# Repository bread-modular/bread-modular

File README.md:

# Bread Modular

An open-source hardware modular synthesizer format designed to be minimalistic
and cost-effective: USB-powered, breadboard-friendly, with analog/digital
modules and MIDI alongside CV & Gate.

## Find your starting point

- **Build or explore:** [modules](modules/),
  [specification](https://github.com/bread-modular/bread-modular/wiki/Specification),
  [common parts](https://github.com/bread-modular/bread-modular/wiki/Common-Parts).
- **Set up KiCad libraries:** [workspace/library setup](opt/README.md). Projects
  use the shared `opt/fp-lib-table`; initialization copies local submodules
  rather than cloning them.
- **Check/export/source parts:** [KiCad toolkit](opt/kicad-tools/README.md).
  Canonical tools, JLCPCB utilities and skills live under `opt/kicad-tools/`.

## KiCad quick start

```sh
python3 -B opt/kicad-tools/kicad_tools.py --help
python3 -B opt/kicad-tools/kicad_tools.py doctor
python3 -B opt/kicad-tools/kicad_tools.py export --help
```

Python + installed KiCad CLI; no extra packages for core tools. Private checks,
Gerber/BOM/CPL export, native netlist helpers and read-only sourcing have
[distinct requirements and safety boundaries](opt/kicad-tools/README.md).
Exports are not electrical/release/order approval; keep frozen module scripts
and production designs untouched. Historical `opt/kicad-jlcpcb` and
`.agents/skills/{kicad-workflow,jlcpcb-assembly}` resolve through
[relative compatibility symlinks](opt/kicad-tools/BUNDLING.md#canonical-layout).

Agents: start with the [KiCad workflow skill](opt/kicad-tools/skills/kicad-workflow/SKILL.md)
or [assembly skill](opt/kicad-tools/skills/jlcpcb-assembly/SKILL.md), then actual CLI help.

## Project references

[Module catalog](https://github.com/bread-modular/bread-modular/wiki/Modules) ·
[Modular MIDI](https://github.com/bread-modular/bread-modular/wiki/Modular-MIDI) ·
[PCB assembly](https://github.com/bread-modular/bread-modular/wiki/PCB-Assembly)

- [Standalone exporter / native part-number setup](opt/kicad-tools/jlcpcb/README.md)
- [Sourcing, audits and passive planning](opt/kicad-tools/jlcpcb/ASSEMBLY.md)
- [32bit-5v sourcing / release HOLD](modules/32bit-5v/verification/basic-economy/README.md)
- [16bit-5v sourcing HOLD evidence](modules/16bit-5v/verification/basic-economy/README.md)

<details>
<summary>Project image and full feature overview</summary>

- **Modular design:** Just like Eurorack.
- **USB-powered:** It can be portable.
- **Minimal design:** Cost-effective.
- **Modular MIDI support:** Communicate between modules; CV & Gate still supported.
- **Analog and digital signal paths:** It’s your choice.
- **Diverse built-in modules:** A wide range of pre-designed modules.
- **Configurable digital modules:** Voice and CV using AtTiny 1616 or ESP32.
- **Fully open source:** Schematics, PCB designs and code.
- **Ease of customization:** Create modules tailored to your needs.
- **No case required:** Use directly on a breadboard or a simple base module.

</details>

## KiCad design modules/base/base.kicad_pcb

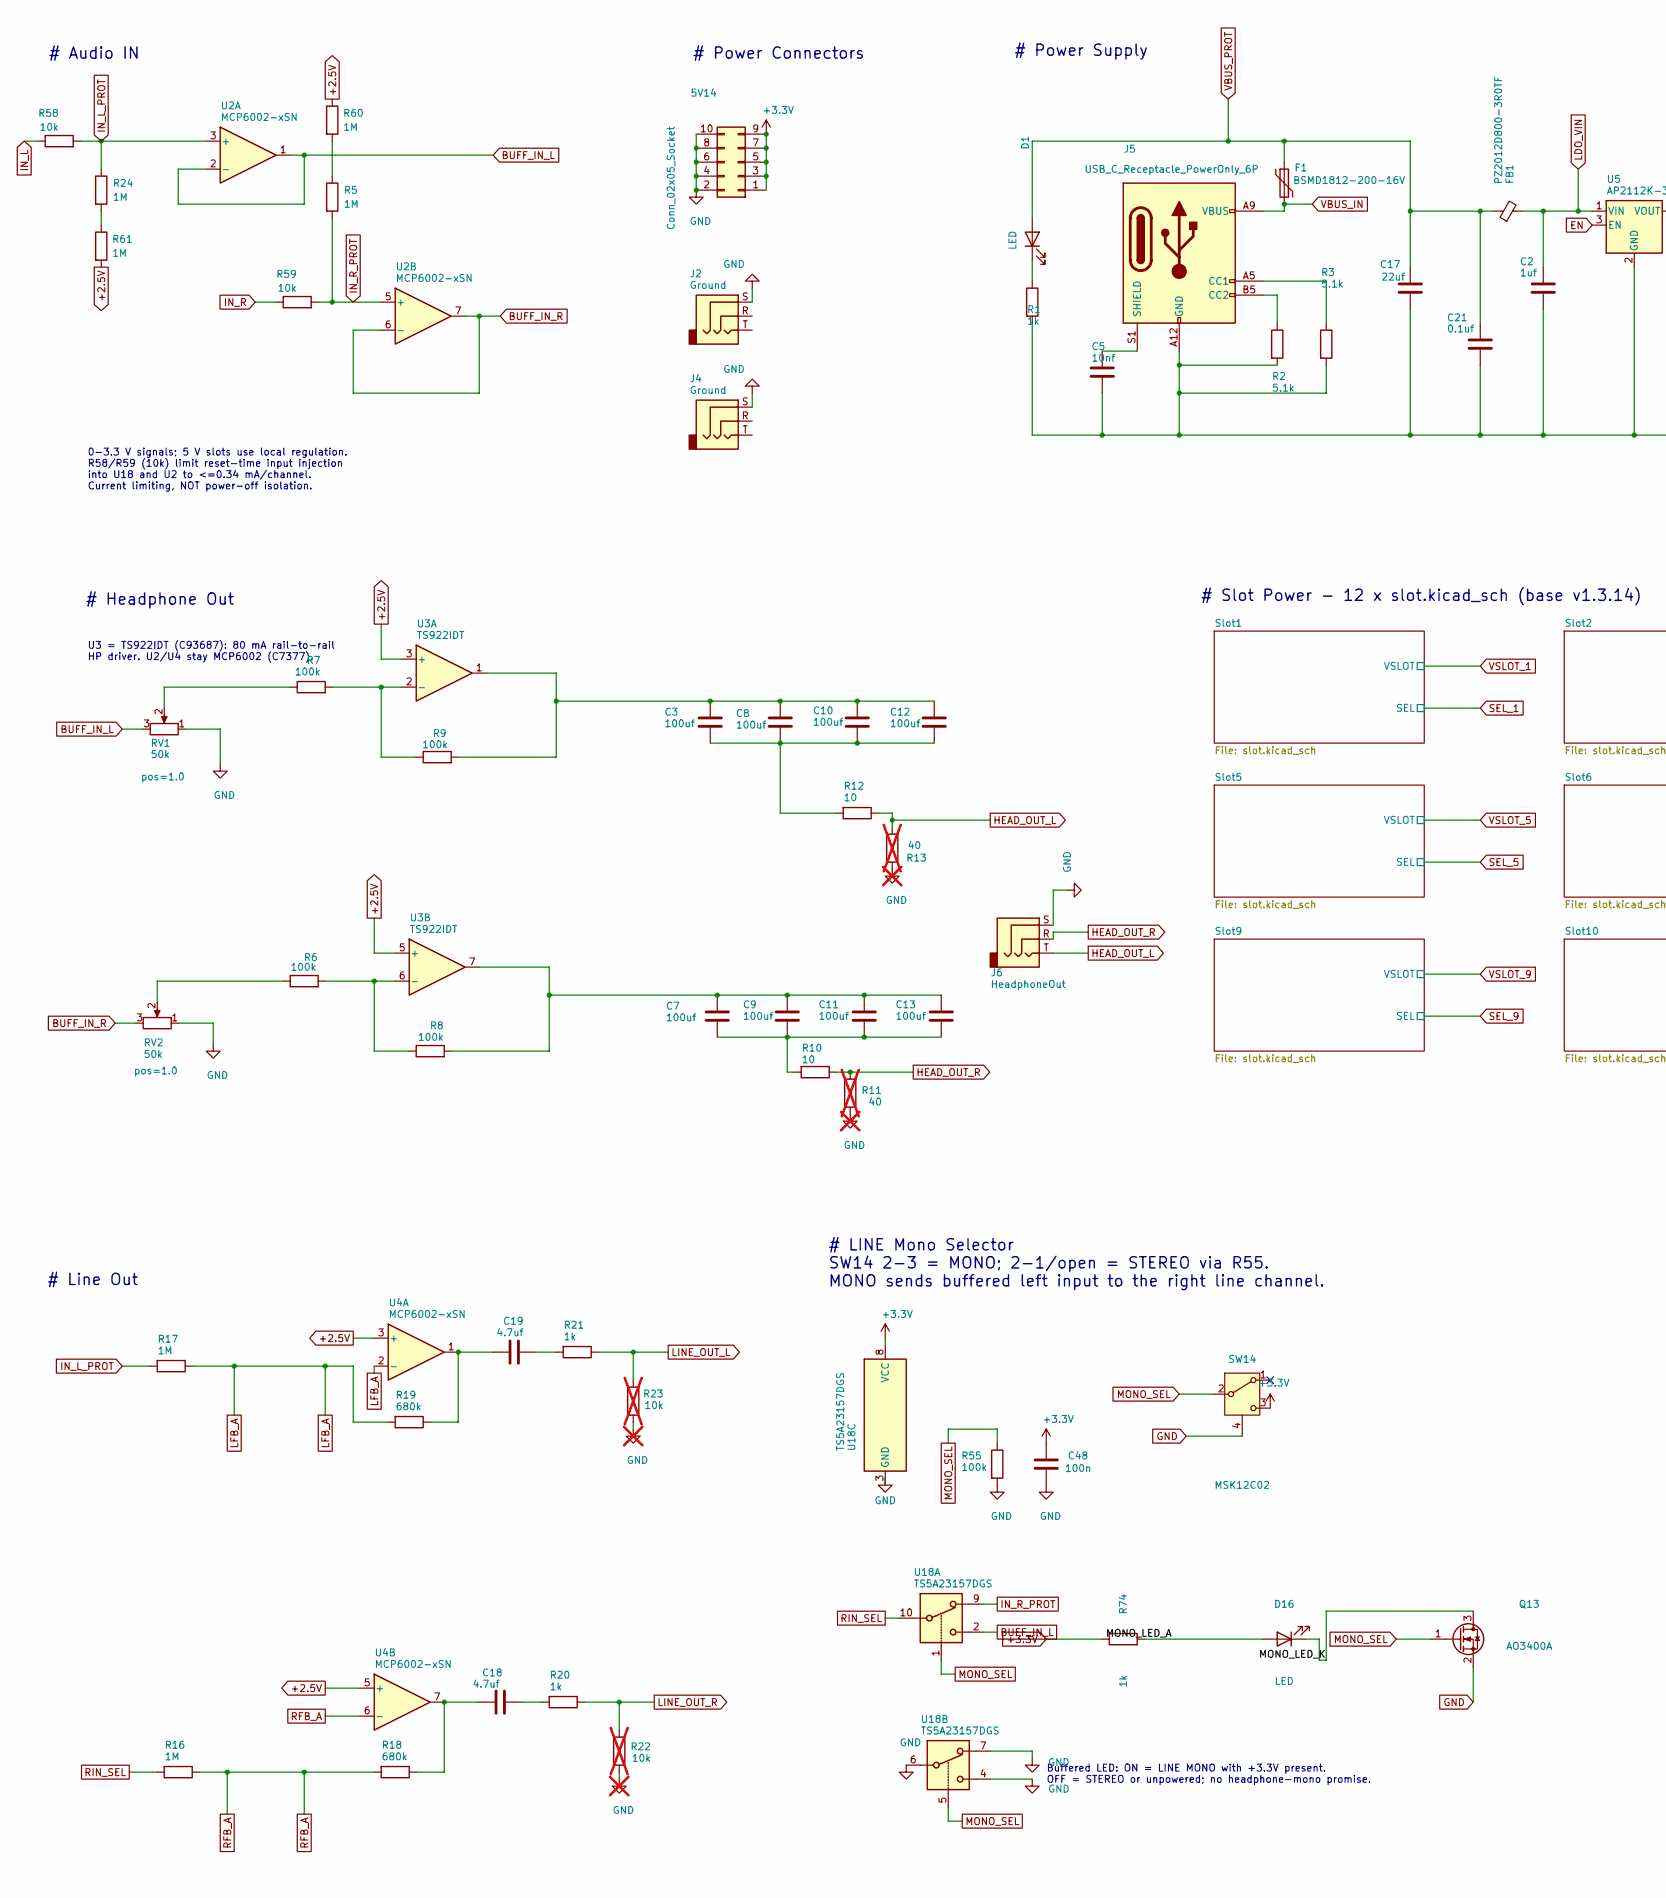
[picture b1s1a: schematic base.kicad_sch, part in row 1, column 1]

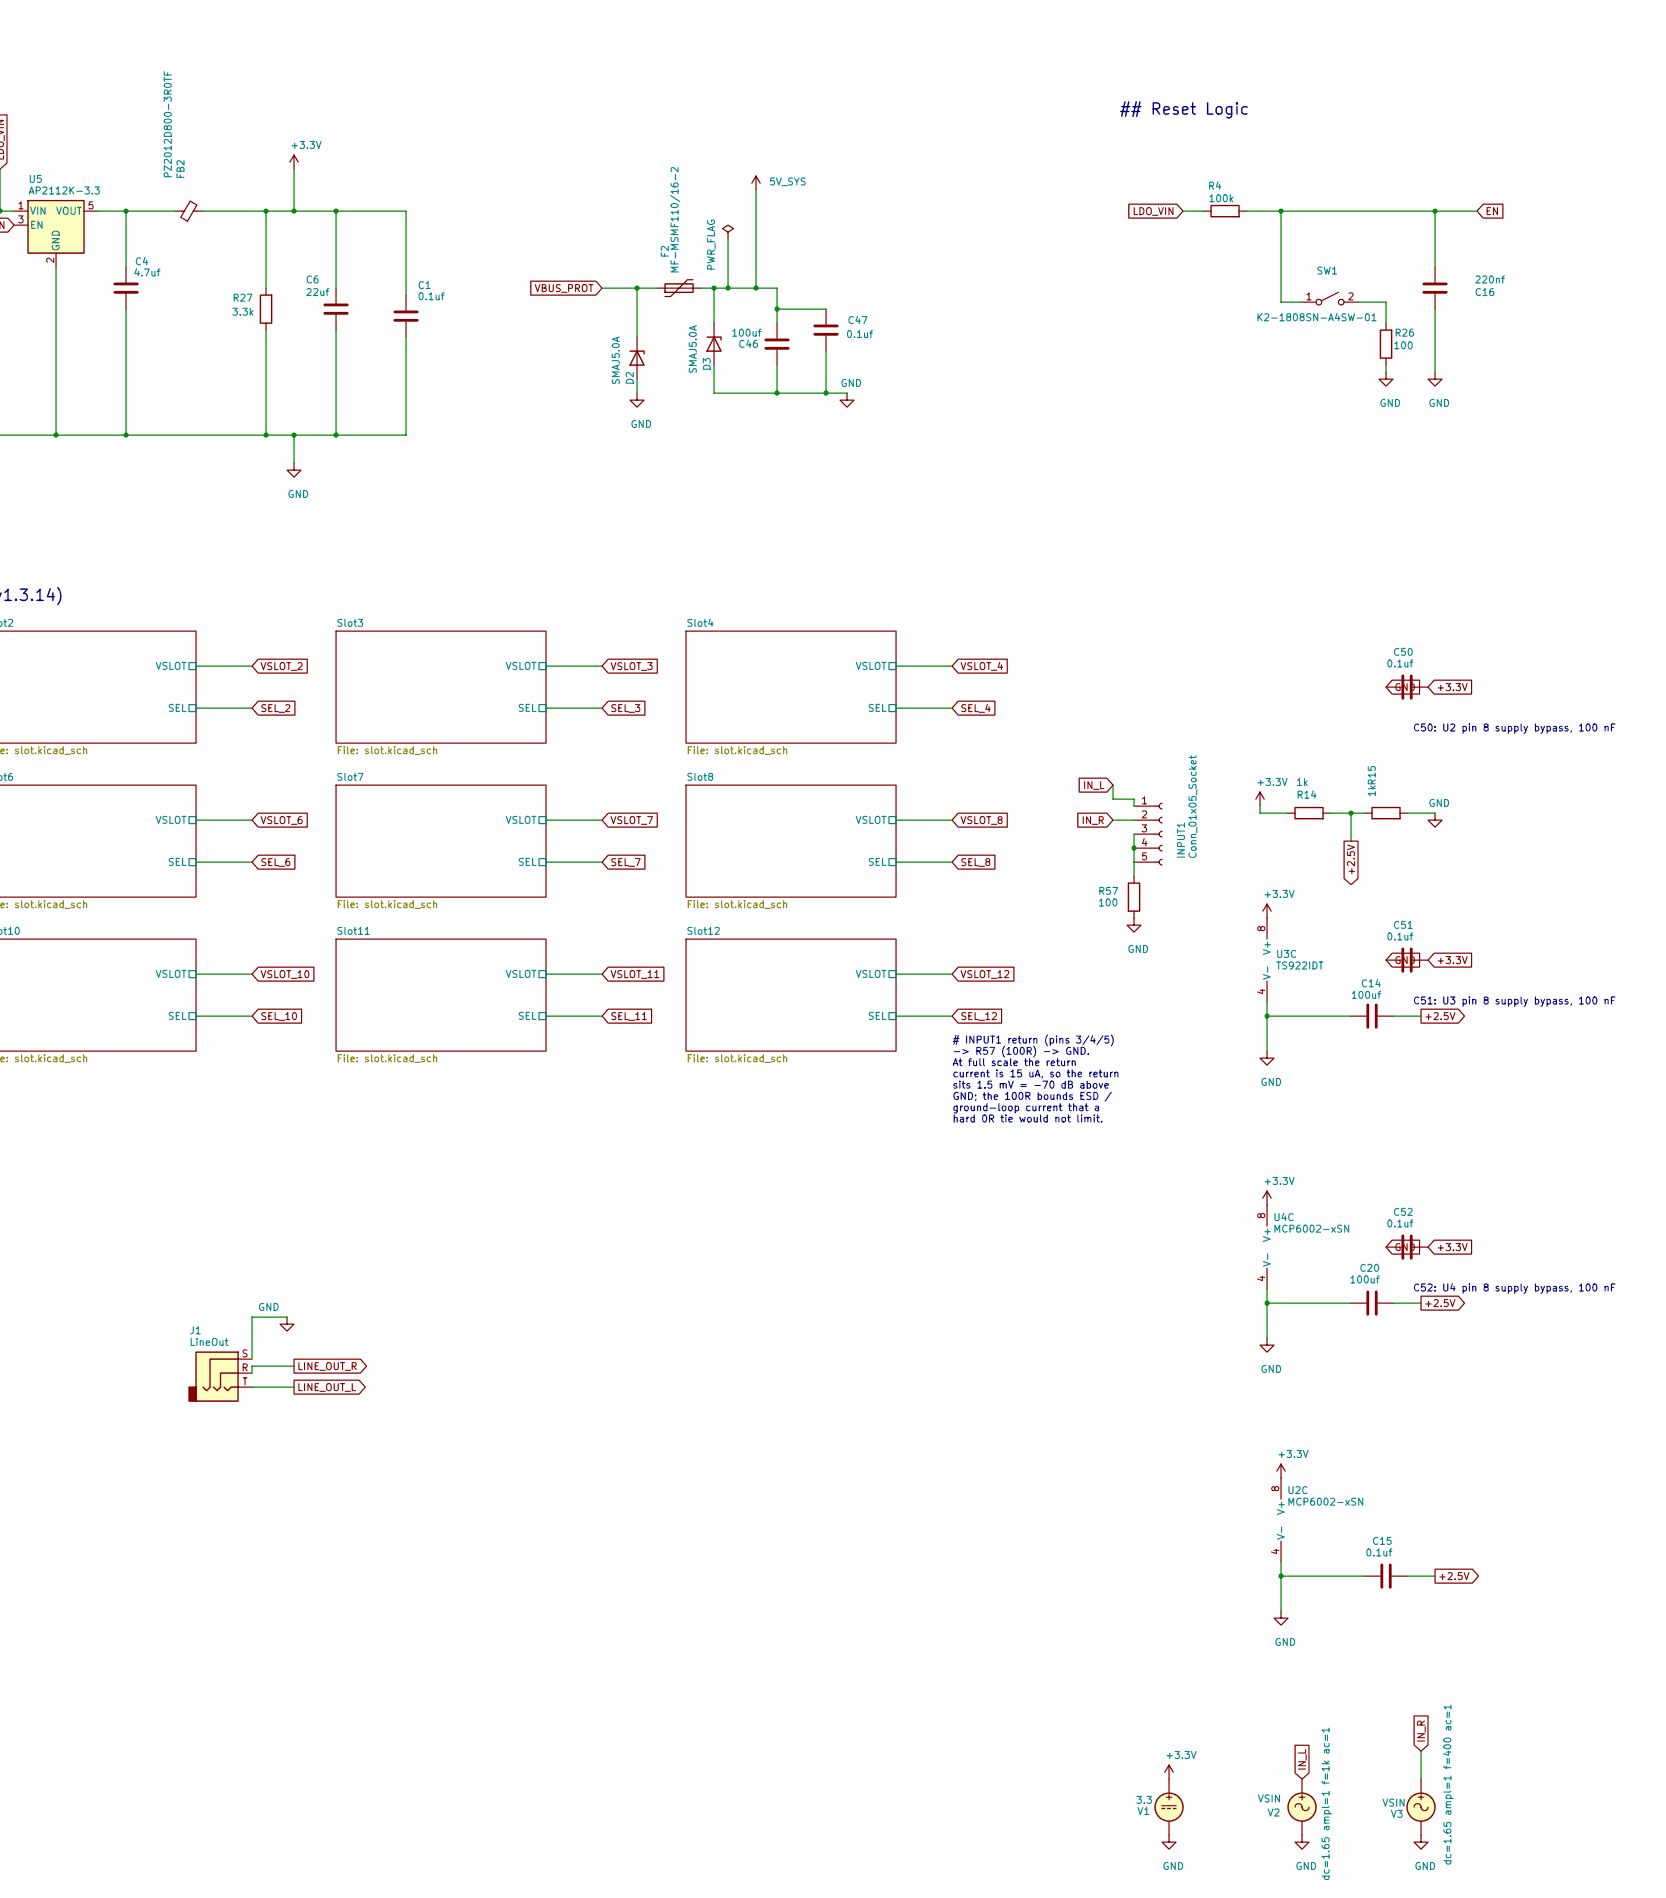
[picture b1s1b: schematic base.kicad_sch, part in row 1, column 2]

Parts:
5V14: Conn_02x05_Socket; PinSocket_2x05_P2.54mm_Vertical; MPN PZ254-2-05-Z-8.5; LCSC C2894966
C1, C15, C21, C47, C50, C51, C52: 0.1uf; C_0402_1005Metric; MPN CL05B104KO5NNNC; LCSC C1525
C2: 1uf; C_0805_2012Metric; MPN CL21B105KBFNNNE; LCSC C28323
C3, C7, C8, C9, C10, C11, C12, C13, C14, C20, C46: 100uf; C_1206_3216Metric; MPN CL31A107MQHNNNE; LCSC C15008
C4: 4.7uf; C_0805_2012Metric; MPN CL21A475KAQNNNE; LCSC C1779
C5: 10nf; C_0805_2012Metric; MPN CL21B103KBANNNC; LCSC C1710
C6, C17: 22uf; C_1206_3216Metric; MPN CL31A226KAHNNNE; LCSC C12891
C16: 220nf; C_0402_1005Metric; MPN CL05B224KO5NNNC; LCSC C16772
C18, C19: 4.7uf; C_0603_1608Metric; MPN CL10A475KO8NNNC; LCSC C19666
C48: 100n; C_0402_1005Metric; MPN CL05B104KO5NNNC; LCSC C1525
D1, D16: LED; LED_0603_1608Metric; MPN KT-0603R; LCSC C2286
D2, D3: SMAJ5.0A; D_SMA; MPN SMAJ5.0A/TR13; LCSC C78401
F1: BSMD1812-200-16V; Fuse_1812_4532Metric; MPN BSMD1812-200-16V; LCSC C883156
F2: MF-MSMF110/16-2; Fuse_1812_4532Metric; MPN MF-MSMF110/16-2; LCSC C210834
FB1, FB2: PZ2012D800-3R0TF; C_0805_2012Metric; MPN PZ2012D800-3R0TF; LCSC C12389
INPUT1: Conn_01x05_Socket; PinSocket_1x05_P2.54mm_Vertical; MPN PZ254-1-05-Z-8.5; LCSC C2894928
J1: LineOut; Jack_3.5mm_QingPu_WQP-PJ366ST_Vertical; MPN WQP-PJ366ST; LCSC NOT-JLC
J2, J4: Ground; Jack_3.5mm_QingPu_WQP-PJ366ST_Vertical; MPN WQP-PJ366ST; LCSC NOT-JLC
J5: USB_C_Receptacle_PowerOnly_6P; HRO-TYPE-C-31-M-12; MPN TYPE-C-31-M-12; LCSC C165948
J6: HeadphoneOut; Jack_3.5mm_QingPu_WQP-PJ366ST_Vertical; MPN WQP-PJ366ST; LCSC NOT-JLC
Q13: AO3400A; SOT-23; MPN AO3400A; LCSC C20917
R1, R14, R15, R20, R21, R74: 1k; R_0402_1005Metric; MPN 0402WGF1001TCE; LCSC C11702
R2, R3: 5.1k; R_0603_1608Metric; MPN 0603WAF5101T5E; LCSC C23186
R4, R6, R7, R8, R9, R55: 100k; R_0402_1005Metric; MPN 0402WGF1003TCE; LCSC C25741
R5, R16, R17, R24, R60, R61: 1M; R_0402_1005Metric; MPN 0402WGF1004TCE; LCSC C26083
R10, R12: 10; R_1206_3216Metric; MPN 1206W4F100JT5E; LCSC C17903
R11: 40; MPN N/A-SIM; LCSC N/A-SIM; not fitted
R13: 40; R_0402_1005Metric; MPN N/A-SIM; LCSC N/A-SIM; not fitted
R18, R19: 680k; R_0603_1608Metric; MPN 0603WAF6803T5E; LCSC C25822
R22, R23: 10k; MPN N/A-SIM; LCSC N/A-SIM; not fitted
R26, R57: 100; R_0402_1005Metric; MPN 0402WGF1000TCE; LCSC C25076
R27: 3.3k; R_0402_1005Metric; MPN 0402WGF3301TCE; LCSC C25890
R58, R59: 10k; R_0402_1005Metric; MPN 0402WGF1002TCE; LCSC C25744
RV1, RV2: 50k; Potentiometer_RV09; MPN RV09-50K; LCSC NOT-JLC
SW1: K2-1808SN-A4SW-01; MPN K2-1808SN-A4SW-01; LCSC C92589
SW14: MSK12C02; SW_SPDT_Shouhan_MSK12C02_C431540; MPN MSK12C02; LCSC C431540
U2, U4: MCP6002-xSN; SOIC-8_3.9x4.9mm_P1.27mm; MPN MCP6002T-I/SN; LCSC C7377
U3: TS922IDT; SOIC-8_3.9x4.9mm_P1.27mm; MPN TS922IDT; LCSC C93687
U5: AP2112K-3.3; SOT-23-5; MPN AP2112K-3.3TRG1; LCSC C51118
U18: TS5A23157DGS; TSSOP-10_3x3mm_P0.5mm; MPN TS5A23157DGSR; LCSC C11133
V1: 3.3; MPN N/A-SIM; LCSC N/A-SIM
V2, V3: VSIN; MPN N/A-SIM; LCSC N/A-SIM

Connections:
5V_SYS: C46.1, C47.1, D3.1 (K), F2.2; also elsewhere on the board
+2.5V: C14.2, C15.2, C20.2, R14.2, R15.1, R60.1, R61.2, U3.3 (+), U3.5 (+), U4.3 (+), U4.5 (+)
+3.3V: 5V14.1, 5V14.3, 5V14.5, 5V14.7, 5V14.9, C1.1, C6.1, C48.1, C50.2, C51.2, C52.2, FB2.2, R14.1, R27.2, R74.1, SW14.3 (C), U2.8 (V+), U3.8 (V+), U4.8 (V+), U18.8 (VCC), V1.1; also elsewhere on the board
/MONO_LED_A: D16.2 (A), R74.2
/MONO_LED_K: D16.1 (K), Q13.3 (D)
BUFF_IN_L: RV1.3, U2.1, U2.2 (-), U18.2
BUFF_IN_R: RV2.3, U2.6 (-), U2.7
EN: C16.1, R4.2, SW1.1 (A), U5.3 (EN)
GND: 5V14.2, 5V14.4, 5V14.6, 5V14.8, 5V14.10, C1.2, C2.2, C4.2, C5.2, C6.2, C14.1, C15.1, C16.2, C17.2, C20.1, C21.2, C46.2, C47.2, C48.2, C50.1, C51.1, C52.1, D2.2 (A), D3.2 (A), J1.S, J2.S, J4.S, J5.A12 (GND), J5.B12 (GND), J6.S, Q13.2 (S), R1.2, R2.2, R3.2, R11.1, R13.1, R15.2, R22.1, R23.1, R26.1, R27.1, R55.2, R57.2, RV1.1, RV2.1, SW14.4 (SHIELD), U2.4 (V-), U3.4 (V-), U4.4 (V-), U5.2 (GND), U18.3 (GND), U18.4, U18.6, U18.7, V1.2, V2.2, V3.2; also elsewhere on the board
HEAD_OUT_L: J6.T, R12.1, R13.2
HEAD_OUT_R: J6.R, R10.1, R11.2
IN_L: INPUT1.1, R58.1, V2.1
IN_L_PROT: R17.2, R24.1, R58.2, U2.3 (+)
IN_R: INPUT1.2, R59.1, V3.1
IN_R_PROT: R5.2, R59.2, U2.5 (+), U18.9
LDO_VIN: C2.1, FB1.2, R4.1, U5.1 (VIN)
LFB_A: R17.1, R19.2, U4.2 (-)
LINE_OUT_L: J1.T, R21.1, R23.2
LINE_OUT_R: J1.R, R20.1, R22.2
MONO_SEL: Q13.1 (G), R55.1, SW14.2 (B), U18.1, U18.5
unnamed: C3.1, C8.1, C10.1, C12.1, R9.2, U3.1
unnamed: C3.2, C8.2, C10.2, C12.2, R12.2
unnamed: C7.1, C9.1, C11.1, C13.1, R8.2, U3.7
unnamed: C7.2, C9.2, C11.2, C13.2, R10.2
unnamed: C18.1, R18.1, U4.7
unnamed: C18.2, R20.2
unnamed: C19.1, R19.1, U4.1
unnamed: C19.2, R21.2
unnamed: D1.1 (K), R1.1
unnamed: INPUT1.3, INPUT1.4, INPUT1.5, R57.1
unnamed: J5.A5 (CC1), R3.1
unnamed: J5.B5 (CC2), R2.1
unnamed: C5.1, J5.S1 (SHIELD)
unnamed: R5.1, R60.2
unnamed: R6.1, RV2.2
unnamed: R7.1, RV1.2
unnamed: R24.2, R61.1
unnamed: R26.2, SW1.2 (B)
unnamed: R7.2, R9.1, U3.2 (-)
unnamed: R6.2, R8.1, U3.6 (-)
unnamed: C4.1, FB2.1, U5.5 (VOUT)
RFB_A: R16.1, R18.2, U4.6 (-)
RIN_SEL: R16.2, U18.10
VBUS_IN: F1.2, J5.A9 (VBUS), J5.B9 (VBUS)
VBUS_PROT: C17.1, C21.1, D1.2 (A), D2.1 (K), F1.1, F2.1, FB1.1; also elsewhere on the board

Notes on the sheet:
Buffered LED: ON = LINE MONO with +3.3V present. OFF = STEREO or unpowered; no headphone-mono promise.
## Reset Logic
# Slot Power - 12 x slot.kicad_sch (base v1.3.14)
# INPUT1 return (pins 3/4/5) -> R57 (100R) -> GND. At full scale the return current is 15 uA, so the return sits 1.5 mV = -70 dB above GND; the 100R bounds ESD / ground-loop current that a hard 0R tie would not limit.
# Power Supply
# Audio IN
C51: U3 pin 8 supply bypass, 100 nF
0-3.3 V signals; 5 V slots use local regulation. R58/R59 (10k) limit reset-time input injection into U18 and U2 to <=0.34 mA/channel. Current limiting, NOT power-off isolation.
U3 = TS922IDT (C93687): 80 mA rail-to-rail HP driver. U2/U4 stay MCP6002 (C7377).
C50: U2 pin 8 supply bypass, 100 nF
# LINE Mono Selector SW14 2-3 = MONO; 2-1/open = STEREO via R55. MONO sends buffered left input to the right line channel.
# Headphone Out
# Power Connectors
# Line Out
C52: U4 pin 8 supply bypass, 100 nF

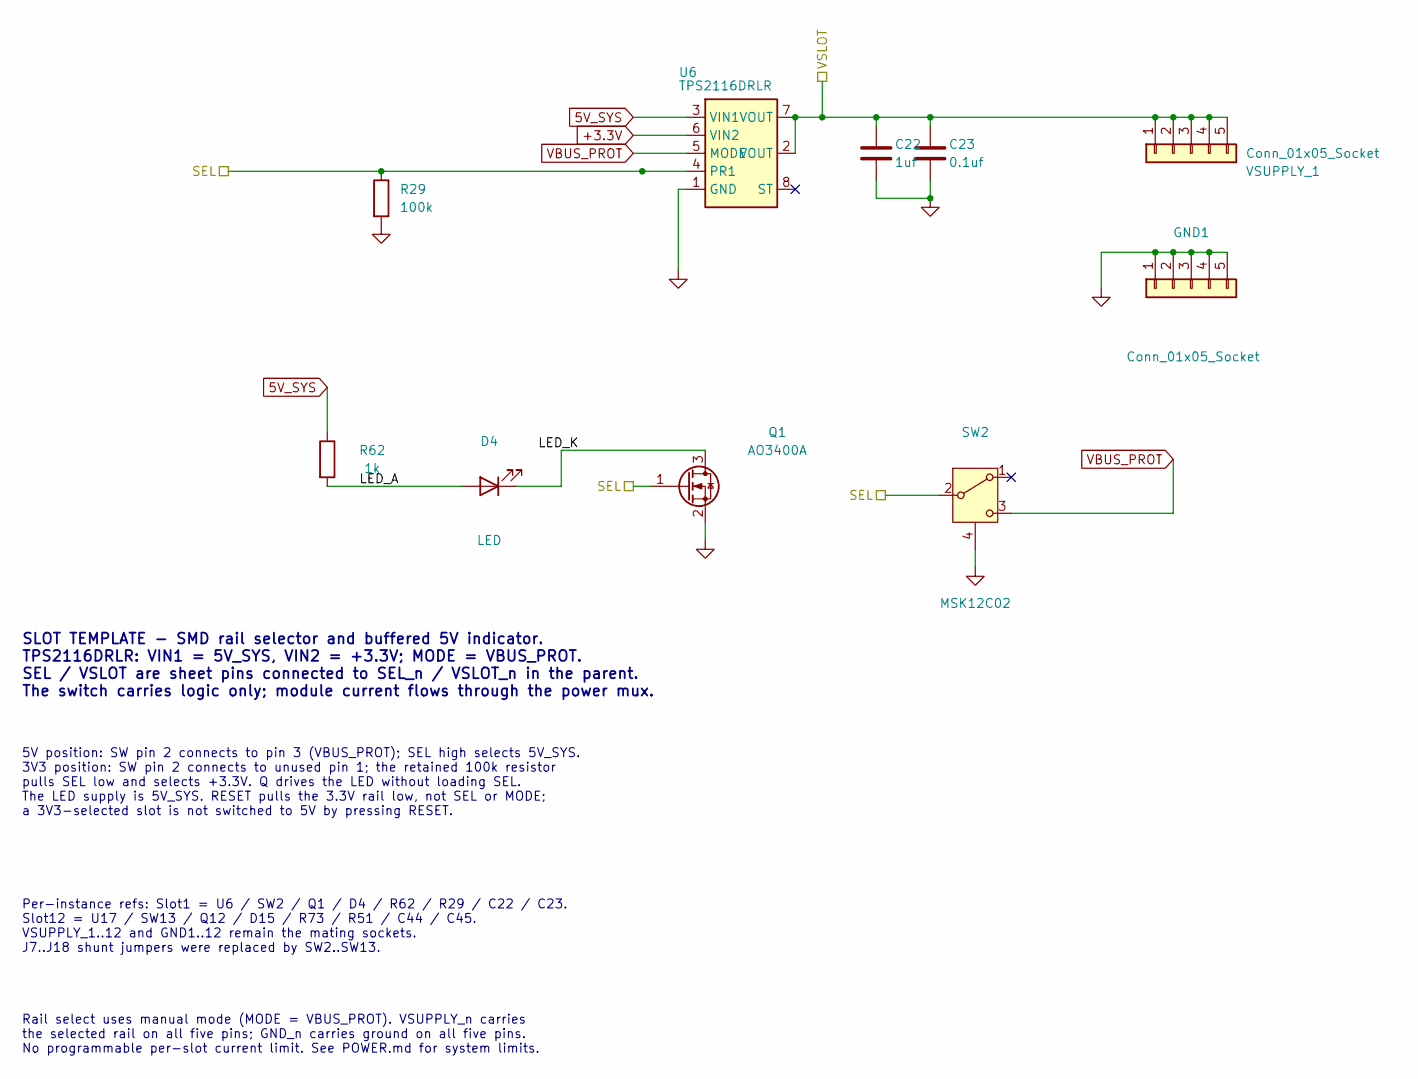
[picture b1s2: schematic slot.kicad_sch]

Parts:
C22: 1uf; C_0402_1005Metric; MPN CL05A105KA5NQNC; LCSC C52923
C23: 0.1uf; C_0402_1005Metric; MPN CL05B104KO5NNNC; LCSC C1525
D4: LED; LED_0603_1608Metric; MPN KT-0603R; LCSC C2286
GND1: Conn_01x05_Socket; Power_Connector; MPN PZ254-1-05-Z-8.5; LCSC C2894928
Q1: AO3400A; SOT-23; MPN AO3400A; LCSC C20917
R29: 100k; R_0402_1005Metric; MPN 0402WGF1003TCE; LCSC C25741
R62: 1k; R_0402_1005Metric; MPN 0402WGF1001TCE; LCSC C11702
SW2: MSK12C02; SW_SPDT_Shouhan_MSK12C02_C431540; MPN MSK12C02; LCSC C431540
U6: TPS2116DRLR; SOT-583-8; MPN TPS2116DRLR; LCSC C3235557
VSUPPLY_1: Conn_01x05_Socket; Power_Connector; MPN PZ254-1-05-Z-8.5; LCSC C2894928

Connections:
5V_SYS: R62.1, U6.3 (VIN1); also elsewhere on the board
+3.3V: U6.6 (VIN2); also elsewhere on the board
/Slot1/LED_A: D4.2 (A), R62.2
/Slot1/LED_K: D4.1 (K), Q1.3 (D)
GND: C22.2, C23.2, GND1.1, GND1.2, GND1.3, GND1.4, GND1.5, Q1.2 (S), R29.2, SW2.4 (SHIELD), U6.1 (GND); also elsewhere on the board
SEL_1: Q1.1 (G), R29.1, SW2.2 (B), U6.4 (PR1)
VBUS_PROT: SW2.3 (C), U6.5 (MODE); also elsewhere on the board
VSLOT_1: C22.1, C23.1, U6.2 (VOUT), U6.7 (VOUT), VSUPPLY_1.1, VSUPPLY_1.2, VSUPPLY_1.3, VSUPPLY_1.4, VSUPPLY_1.5

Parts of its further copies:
C24, C26, C28, C30, C32, C34, C36, C38, C40, C42, C44: 1uf; C_0402_1005Metric; MPN CL05A105KA5NQNC; LCSC C52923
C25, C27, C29, C31, C33, C35, C37, C39, C41, C43, C45: 0.1uf; C_0402_1005Metric; MPN CL05B104KO5NNNC; LCSC C1525
D5, D6, D7, D8, D9, D10, D11, D12, D13, D14, D15: LED; LED_0603_1608Metric; MPN KT-0603R; LCSC C2286
GND2, GND3, GND4, GND5, GND6, GND7, GND8, GND9, GND10, GND11, GND12: Conn_01x05_Socket; Power_Connector; MPN PZ254-1-05-Z-8.5; LCSC C2894928
Q2, Q3, Q4, Q5, Q6, Q7, Q8, Q9, Q10, Q11, Q12: AO3400A; SOT-23; MPN AO3400A; LCSC C20917
R31, R33, R35, R37, R39, R41, R43, R45, R47, R49, R51: 100k; R_0402_1005Metric; MPN 0402WGF1003TCE; LCSC C25741
R63, R64, R65, R66, R67, R68, R69, R70, R71, R72, R73: 1k; R_0402_1005Metric; MPN 0402WGF1001TCE; LCSC C11702
SW3, SW4, SW5, SW6, SW7, SW8, SW9, SW10, SW11, SW12, SW13: MSK12C02; SW_SPDT_Shouhan_MSK12C02_C431540; MPN MSK12C02; LCSC C431540
U7, U8, U9, U10, U11, U12, U13, U14, U15, U16, U17: TPS2116DRLR; SOT-583-8; MPN TPS2116DRLR; LCSC C3235557
VSUPPLY_2, VSUPPLY_3, VSUPPLY_4, VSUPPLY_5, VSUPPLY_6, VSUPPLY_7, VSUPPLY_8, VSUPPLY_9, VSUPPLY_10, VSUPPLY_11, VSUPPLY_12: Conn_01x05_Socket; Power_Connector; MPN PZ254-1-05-Z-8.5; LCSC C2894928

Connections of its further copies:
5V_SYS: R63.1, R64.1, R65.1, R66.1, R67.1, R68.1, R69.1, R70.1, R71.1, R72.1, R73.1, U7.3 (VIN1), U8.3 (VIN1), U9.3 (VIN1), U10.3 (VIN1), U11.3 (VIN1), U12.3 (VIN1), U13.3 (VIN1), U14.3 (VIN1), U15.3 (VIN1), U16.3 (VIN1), U17.3 (VIN1); also elsewhere on the board
+3.3V: U7.6 (VIN2), U8.6 (VIN2), U9.6 (VIN2), U10.6 (VIN2), U11.6 (VIN2), U12.6 (VIN2), U13.6 (VIN2), U14.6 (VIN2), U15.6 (VIN2), U16.6 (VIN2), U17.6 (VIN2); also elsewhere on the board
/Slot2/LED_A: D5.2 (A), R63.2
/Slot2/LED_K: D5.1 (K), Q2.3 (D)
/Slot3/LED_A: D6.2 (A), R64.2
/Slot3/LED_K: D6.1 (K), Q3.3 (D)
/Slot4/LED_A: D7.2 (A), R65.2
/Slot4/LED_K: D7.1 (K), Q4.3 (D)
/Slot5/LED_A: D8.2 (A), R66.2
/Slot5/LED_K: D8.1 (K), Q5.3 (D)
/Slot6/LED_A: D9.2 (A), R67.2
/Slot6/LED_K: D9.1 (K), Q6.3 (D)
/Slot7/LED_A: D10.2 (A), R68.2
/Slot7/LED_K: D10.1 (K), Q7.3 (D)
/Slot8/LED_A: D11.2 (A), R69.2
/Slot8/LED_K: D11.1 (K), Q8.3 (D)
/Slot9/LED_A: D12.2 (A), R70.2
/Slot9/LED_K: D12.1 (K), Q9.3 (D)
/Slot10/LED_A: D13.2 (A), R71.2
/Slot10/LED_K: D13.1 (K), Q10.3 (D)
/Slot11/LED_A: D14.2 (A), R72.2
/Slot11/LED_K: D14.1 (K), Q11.3 (D)
/Slot12/LED_A: D15.2 (A), R73.2
/Slot12/LED_K: D15.1 (K), Q12.3 (D)
GND: C24.2, C25.2, C26.2, C27.2, C28.2, C29.2, C30.2, C31.2, C32.2, C33.2, C34.2, C35.2, C36.2, C37.2, C38.2, C39.2, C40.2, C41.2, C42.2, C43.2, C44.2, C45.2, GND2.1, GND2.2, GND2.3, GND2.4, GND2.5, GND3.1, GND3.2, GND3.3, GND3.4, GND3.5, GND4.1, GND4.2, GND4.3, GND4.4, GND4.5, GND5.1, GND5.2, GND5.3, GND5.4, GND5.5, GND6.1, GND6.2, GND6.3, GND6.4, GND6.5, GND7.1, GND7.2, GND7.3, GND7.4, GND7.5, GND8.1, GND8.2, GND8.3, GND8.4, GND8.5, GND9.1, GND9.2, GND9.3, GND9.4, GND9.5, GND10.1, GND10.2, GND10.3, GND10.4, GND10.5, GND11.1, GND11.2, GND11.3, GND11.4, GND11.5, GND12.1, GND12.2, GND12.3, GND12.4, GND12.5, Q2.2 (S), Q3.2 (S), Q4.2 (S), Q5.2 (S), Q6.2 (S), Q7.2 (S), Q8.2 (S), Q9.2 (S), Q10.2 (S), Q11.2 (S), Q12.2 (S), R31.2, R33.2, R35.2, R37.2, R39.2, R41.2, R43.2, R45.2, R47.2, R49.2, R51.2, SW3.4 (SHIELD), SW4.4 (SHIELD), SW5.4 (SHIELD), SW6.4 (SHIELD), SW7.4 (SHIELD), SW8.4 (SHIELD), SW9.4 (SHIELD), SW10.4 (SHIELD), SW11.4 (SHIELD), SW12.4 (SHIELD), SW13.4 (SHIELD), U7.1 (GND), U8.1 (GND), U9.1 (GND), U10.1 (GND), U11.1 (GND), U12.1 (GND), U13.1 (GND), U14.1 (GND), U15.1 (GND), U16.1 (GND), U17.1 (GND); also elsewhere on the board
SEL_2: Q2.1 (G), R31.1, SW3.2 (B), U7.4 (PR1)
SEL_3: Q3.1 (G), R33.1, SW4.2 (B), U8.4 (PR1)
SEL_4: Q4.1 (G), R35.1, SW5.2 (B), U9.4 (PR1)
SEL_5: Q5.1 (G), R37.1, SW6.2 (B), U10.4 (PR1)
SEL_6: Q6.1 (G), R39.1, SW7.2 (B), U11.4 (PR1)
SEL_7: Q7.1 (G), R41.1, SW8.2 (B), U12.4 (PR1)
SEL_8: Q8.1 (G), R43.1, SW9.2 (B), U13.4 (PR1)
SEL_9: Q9.1 (G), R45.1, SW10.2 (B), U14.4 (PR1)
SEL_10: Q10.1 (G), R47.1, SW11.2 (B), U15.4 (PR1)
SEL_11: Q11.1 (G), R49.1, SW12.2 (B), U16.4 (PR1)
SEL_12: Q12.1 (G), R51.1, SW13.2 (B), U17.4 (PR1)
VBUS_PROT: SW3.3 (C), SW4.3 (C), SW5.3 (C), SW6.3 (C), SW7.3 (C), SW8.3 (C), SW9.3 (C), SW10.3 (C), SW11.3 (C), SW12.3 (C), SW13.3 (C), U7.5 (MODE), U8.5 (MODE), U9.5 (MODE), U10.5 (MODE), U11.5 (MODE), U12.5 (MODE), U13.5 (MODE), U14.5 (MODE), U15.5 (MODE), U16.5 (MODE), U17.5 (MODE); also elsewhere on the board
VSLOT_2: C24.1, C25.1, U7.2 (VOUT), U7.7 (VOUT), VSUPPLY_2.1, VSUPPLY_2.2, VSUPPLY_2.3, VSUPPLY_2.4, VSUPPLY_2.5
VSLOT_3: C26.1, C27.1, U8.2 (VOUT), U8.7 (VOUT), VSUPPLY_3.1, VSUPPLY_3.2, VSUPPLY_3.3, VSUPPLY_3.4, VSUPPLY_3.5
VSLOT_4: C28.1, C29.1, U9.2 (VOUT), U9.7 (VOUT), VSUPPLY_4.1, VSUPPLY_4.2, VSUPPLY_4.3, VSUPPLY_4.4, VSUPPLY_4.5
VSLOT_5: C30.1, C31.1, U10.2 (VOUT), U10.7 (VOUT), VSUPPLY_5.1, VSUPPLY_5.2, VSUPPLY_5.3, VSUPPLY_5.4, VSUPPLY_5.5
VSLOT_6: C32.1, C33.1, U11.2 (VOUT), U11.7 (VOUT), VSUPPLY_6.1, VSUPPLY_6.2, VSUPPLY_6.3, VSUPPLY_6.4, VSUPPLY_6.5
VSLOT_7: C34.1, C35.1, U12.2 (VOUT), U12.7 (VOUT), VSUPPLY_7.1, VSUPPLY_7.2, VSUPPLY_7.3, VSUPPLY_7.4, VSUPPLY_7.5
VSLOT_8: C36.1, C37.1, U13.2 (VOUT), U13.7 (VOUT), VSUPPLY_8.1, VSUPPLY_8.2, VSUPPLY_8.3, VSUPPLY_8.4, VSUPPLY_8.5
VSLOT_9: C38.1, C39.1, U14.2 (VOUT), U14.7 (VOUT), VSUPPLY_9.1, VSUPPLY_9.2, VSUPPLY_9.3, VSUPPLY_9.4, VSUPPLY_9.5
VSLOT_10: C40.1, C41.1, U15.2 (VOUT), U15.7 (VOUT), VSUPPLY_10.1, VSUPPLY_10.2, VSUPPLY_10.3, VSUPPLY_10.4, VSUPPLY_10.5
VSLOT_11: C42.1, C43.1, U16.2 (VOUT), U16.7 (VOUT), VSUPPLY_11.1, VSUPPLY_11.2, VSUPPLY_11.3, VSUPPLY_11.4, VSUPPLY_11.5
VSLOT_12: C44.1, C45.1, U17.2 (VOUT), U17.7 (VOUT), VSUPPLY_12.1, VSUPPLY_12.2, VSUPPLY_12.3, VSUPPLY_12.4, VSUPPLY_12.5

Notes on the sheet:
SLOT TEMPLATE - SMD rail selector and buffered 5V indicator. TPS2116DRLR: VIN1 = 5V_SYS, VIN2 = +3.3V; MODE = VBUS_PROT. SEL / VSLOT are sheet pins connected to SEL_n / VSLOT_n in the parent. The switch carries logic only; module current flows through the power mux.
Rail select uses manual mode (MODE = VBUS_PROT). VSUPPLY_n carries the selected rail on all five pins; GND_n carries ground on all five pins. No programmable per-slot current limit. See POWER.md for system limits.
5V position: SW pin 2 connects to pin 3 (VBUS_PROT); SEL high selects 5V_SYS. 3V3 position: SW pin 2 connects to unused pin 1; the retained 100k resistor pulls SEL low and selects +3.3V. Q drives the LED without loading SEL. The LED supply is 5V_SYS. RESET pulls the 3.3V rail low, not SEL or MODE; 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
Per-instance refs: Slot1 = U6 / SW2 / Q1 / D4 / R62 / R29 / C22 / C23. Slot12 = U17 / SW13 / Q12 / D15 / R73 / R51 / C44 / C45. VSUPPLY_1..12 and GND1..12 remain the mating sockets. J7..J18 shunt jumpers were replaced by SW2..SW13.

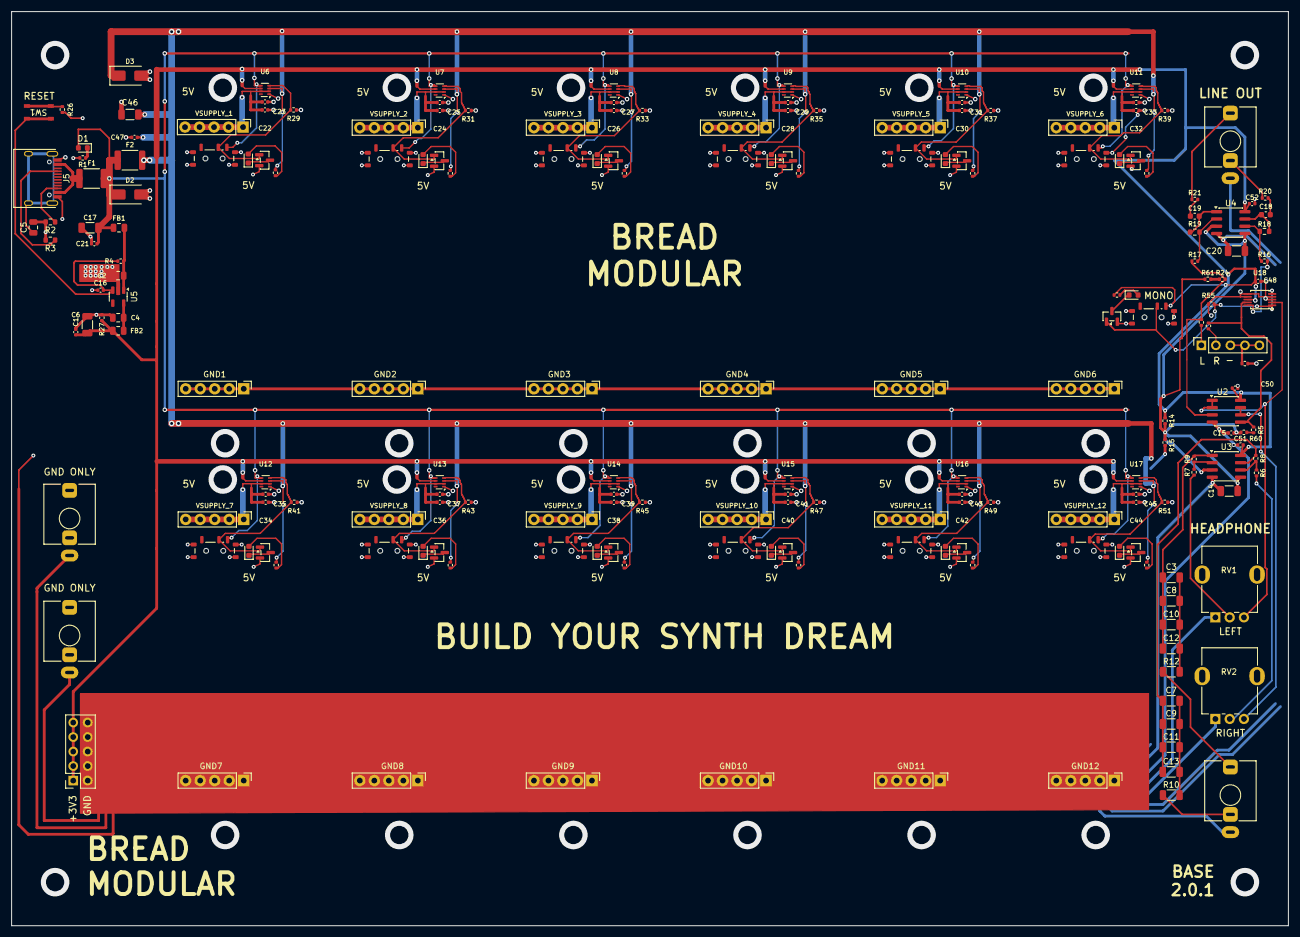
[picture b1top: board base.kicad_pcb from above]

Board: 2 copper layers, 223.5 x 160.0 mm, 201 parts (0 on the bottom side), 93 nets.

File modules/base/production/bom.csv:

Designator,Footprint,Quantity,Value,LCSC Part #,DNP
5V14,Connector_PinSocket_2.54mm:PinSocket_2x05_P2.54mm_Vertical,1,Conn_02x05_Socket,NOT-JLC,
"C1,C15,C21,C23,C25,C27,C29,C31,C33,C35,C37,C39,C41,C43,C45,C47,C50,C51,C52",Capacitor_SMD:C_0402_1005Metric,19,0.1uf,C1525,
C2,Capacitor_SMD:C_0805_2012Metric,1,1uf,C28323,
"C3,C7,C8,C9,C10,C11,C12,C13,C14,C20",Capacitor_SMD:C_1206_3216Metric,10,100uf,C15008,
C4,Capacitor_SMD:C_0805_2012Metric,1,4.7uf,C1779,
C5,Capacitor_SMD:C_0805_2012Metric,1,10nf,C472806,
"C6,C17",Capacitor_SMD:C_1206_3216Metric,2,22uf,C90146,
C16,Capacitor_SMD:C_0402_1005Metric,1,220nf,C16772,
"C18,C19",Capacitor_SMD:C_0603_1608Metric,2,4.7uf,C1705,
"C22,C24,C26,C28,C30,C32,C34,C36,C38,C40,C42,C44",Capacitor_SMD:C_0402_1005Metric,12,1uf,C52923,
C46,Capacitor_SMD:C_1210_3225Metric,1,100uf,C394395,
C48,Capacitor_SMD:C_0402_1005Metric,1,100n,C1525,
D1,LED_SMD:LED_0603_1608Metric,1,LED,C2286,
"D2,D3",Diode_SMD:D_SMA,2,SMAJ5.0A,C78401,
F1,Fuse:Fuse_1812_4532Metric,1,BSMD1812-200-16V,C883156,
F2,Fuse:Fuse_1812_4532Metric,1,MF-MSMF110/16-2,C210834,
"FB1,FB2",Capacitor_SMD:C_0805_2012Metric,2,PZ2012D800-3R0TF,C12389,
"GND1,GND2,GND3,GND4,GND5,GND6,GND7,GND8,GND9,GND10,GND11,GND12,VSUPPLY_1,VSUPPLY_2,VSUPPLY_3,VSUPPLY_4,VSUPPLY_5,VSUPPLY_6,VSUPPLY_7,VSUPPLY_8,VSUPPLY_9,VSUPPLY_10,VSUPPLY_11,VSUPPLY_12",BreadModular_MISC:Power_Connector,24,Conn_01x05_Socket,NOT-JLC,
INPUT1,Connector_PinSocket_2.54mm:PinSocket_1x05_P2.54mm_Vertical,1,Conn_01x05_Socket,NOT-JLC,
J1,BreadModular_AudioJacks:Jack_3.5mm_QingPu_WQP-PJ366ST_Vertical,1,LineOut,NOT-JLC,
"J2,J4",BreadModular_AudioJacks:Jack_3.5mm_QingPu_WQP-PJ366ST_Vertical,2,Ground,NOT-JLC,
J5,BreadModular_TypeC:HRO-TYPE-C-31-M-12,1,USB_C_Receptacle_PowerOnly_6P,C165948,
J6,BreadModular_AudioJacks:Jack_3.5mm_QingPu_WQP-PJ366ST_Vertical,1,HeadphoneOut,NOT-JLC,
"J7,J8,J9,J10,J11,J12,J13,J14,J15,J16,J17,J18",Connector_PinHeader_2.00mm:PinHeader_1x02_P2.00mm_Vertical,12,Conn_01x02,C2905948,
J23,Connector_PinHeader_2.00mm:PinHeader_1x02_P2.00mm_Vertical,1,PZ200-1-02-Z,C2905948,DNP
"R1,R14,R15,R20,R21",Resistor_SMD:R_0402_1005Metric,5,1k,C11702,
"R2,R3",Resistor_SMD:R_0603_1608Metric,2,5.1k,C23186,
"R4,R6,R7,R8,R9,R29,R31,R33,R35,R37,R39,R41,R43,R45,R47,R49,R51,R55",Resistor_SMD:R_0402_1005Metric,18,100k,C25741,
"R5,R24",Resistor_SMD:R_0402_1005Metric,2,2M,C11512,
"R10,R12",Resistor_SMD:R_1206_3216Metric,2,10,C17903,
"R16,R17",Resistor_SMD:R_0402_1005Metric,2,1M,C26083,
"R18,R19",Resistor_SMD:R_0603_1608Metric,2,680k,C25822,
"R26,R57",Resistor_SMD:R_0402_1005Metric,2,100,C25076,
R27,Resistor_SMD:R_0402_1005Metric,1,3.3k,C25890,
"R58,R59",Resistor_SMD:R_0402_1005Metric,2,10k,C25744,
"RV1,RV2",BreadModular_Pots:Potentiometer_RV09,2,50k,NOT-JLC,
SW1,BreadModular_MISC:K2-1808SN-A4SW-01,1,K2-1808SN-A4SW-01,C92589,
"U2,U4",Package_SO:SOIC-8_3.9x4.9mm_P1.27mm,2,MCP6002-xSN,C7377,
U3,Package_SO:SOIC-8_3.9x4.9mm_P1.27mm,1,TS922IDT,C93687,
U5,Package_TO_SOT_SMD:SOT-23-5,1,AP2112K-3.3,C51118,
"U6,U7,U8,U9,U10,U11,U12,U13,U14,U15,U16,U17",Package_TO_SOT_SMD:SOT-583-8,12,TPS2116DRLR,C3235557,
U18,Package_SO:TSSOP-10_3x3mm_P0.5mm,1,TS5A23157DGS,C11133,
